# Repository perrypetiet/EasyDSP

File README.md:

# EasyDSP prototype_dev v0.1 development branch.
This is the EasyDSP prototype development library. In this repository you will find the hardware of the EasyDSP as well as the corresponding firmware. In this readme you will find an explanation of how to firmware functions and how to control the EasyDSP using the corresponding communication protocol. Also, you will find the PCB schematics and PCB design without the need to have KiCad and all the corresponding components on hand.

This readme will be updated to display correct and relevant information depending on the branch.

## Table of contents:
- [EasyDSP prototype\_dev v0.1 development branch.](#easydsp-prototype_dev-v01-development-branch)
  - [Table of contents:](#table-of-contents)
  - [Introduction ](#introduction-)
  - [TODO list ](#todo-list-)
  - [Controlling via BLE. ](#controlling-via-ble-)
  - [Python. ](#python-)
  - [Hardware ](#hardware-)

## Introduction 
The goal of this project is to make a cheap and easy to control module in order to do all your audio digital signal processing needs. The EasyDSP could be used for audio crossover, room correction, subwoofer tuning, using [Bass Eq](https://www.avsforum.com/threads/bass-eq-for-filtered-movies.2995212/) and much more. The goal of the project is to be able to control the EasyDSP using a Bluetooth low energy connection. When connected BLE characteristics can be used to control the EasyDSP. The basic structure of the signal processor can be explained with the following image:
</br></br>
The EasyDSP has two inputs and four outputs. The mux makes it possible to connect any input with any output. Every in and output has an equalizer to which five filters can be applied.</br>
The goal of the protoype is to implement the basic functioning of this system while doing it reliably. When this is achieved, functionality can be upgraded.

## TODO list 

- Make the settings store on the EEPROM. ✅
- Implement more filters (Bessel?) for better low pass and high pass.
- Maybe improve Python module for this verstion.

Things to include in next version:
- Better PCB design to improve the noise in the audio signal coming from the Bluetooth antenna (External antenna?).
- RGB status indication LED.
- Case design. (3D printable).
- Start working on GUI app for desktop to control the device.
- More functionality in firmware, more filters and gain control. And overall cleanup. 
- Thinking about serial control via USB.

## Controlling via BLE. 
Easydsp can be controlled with a BLE connection. The BLE implements two different services. The first service is a "selection" service. With this service the channel and eq number that are desired to be changed can be selected. With the channel number characteriscic you can change the channel number. With the isOutput characteristic you can select if it is an input or output channel that is selected. With the eq characteristic you can selected one of the 5 eq's per channel that you wish to change te settings of.

The EQ service implements the EQ data of the selected EQ on the selected channel. This service has characteristics to change the behaviour of the selected EQ. 

## Python. 
Included is a simple python module, easydsp.py, that can be used to control the easydsp over a BLE connection. I have also included a simple Python command line program that uses this module to control the EasyDSP.

## Hardware 
The EasyDSP is based on the ADAU1701 digital signal processor from Analog Devices. The chip is used in I2C control mode. This way, we can control the the signal processor from an external microcontroller during operation. The microcontroller used is an ESP32-S3 in the form a WROOM module to make development of the prototype hardware easier. The board and firmware have the ability to store the EQ, MUX and gain settings on an EEPROM. The EEPROM used is a 24LC128 in an MSOP package. Technically lower storage 24LC EEPROM's can also be used. In order to upload the firmware to the board, the USB connector on the PCB can be used. Firmware can also be uploaded and monitored using an external USB to UART PCB connected to the connector on the main PCB. There is an example board in the hardware folder. Following is the hardware schematic. The schematic can also be opened using KiCad.
</br></br>
The PCB fabrication files can be found in the hardware_design folder. Using these gerber and drill files you can order a PCB from a manufactorer.
</br></br>
</br></br>

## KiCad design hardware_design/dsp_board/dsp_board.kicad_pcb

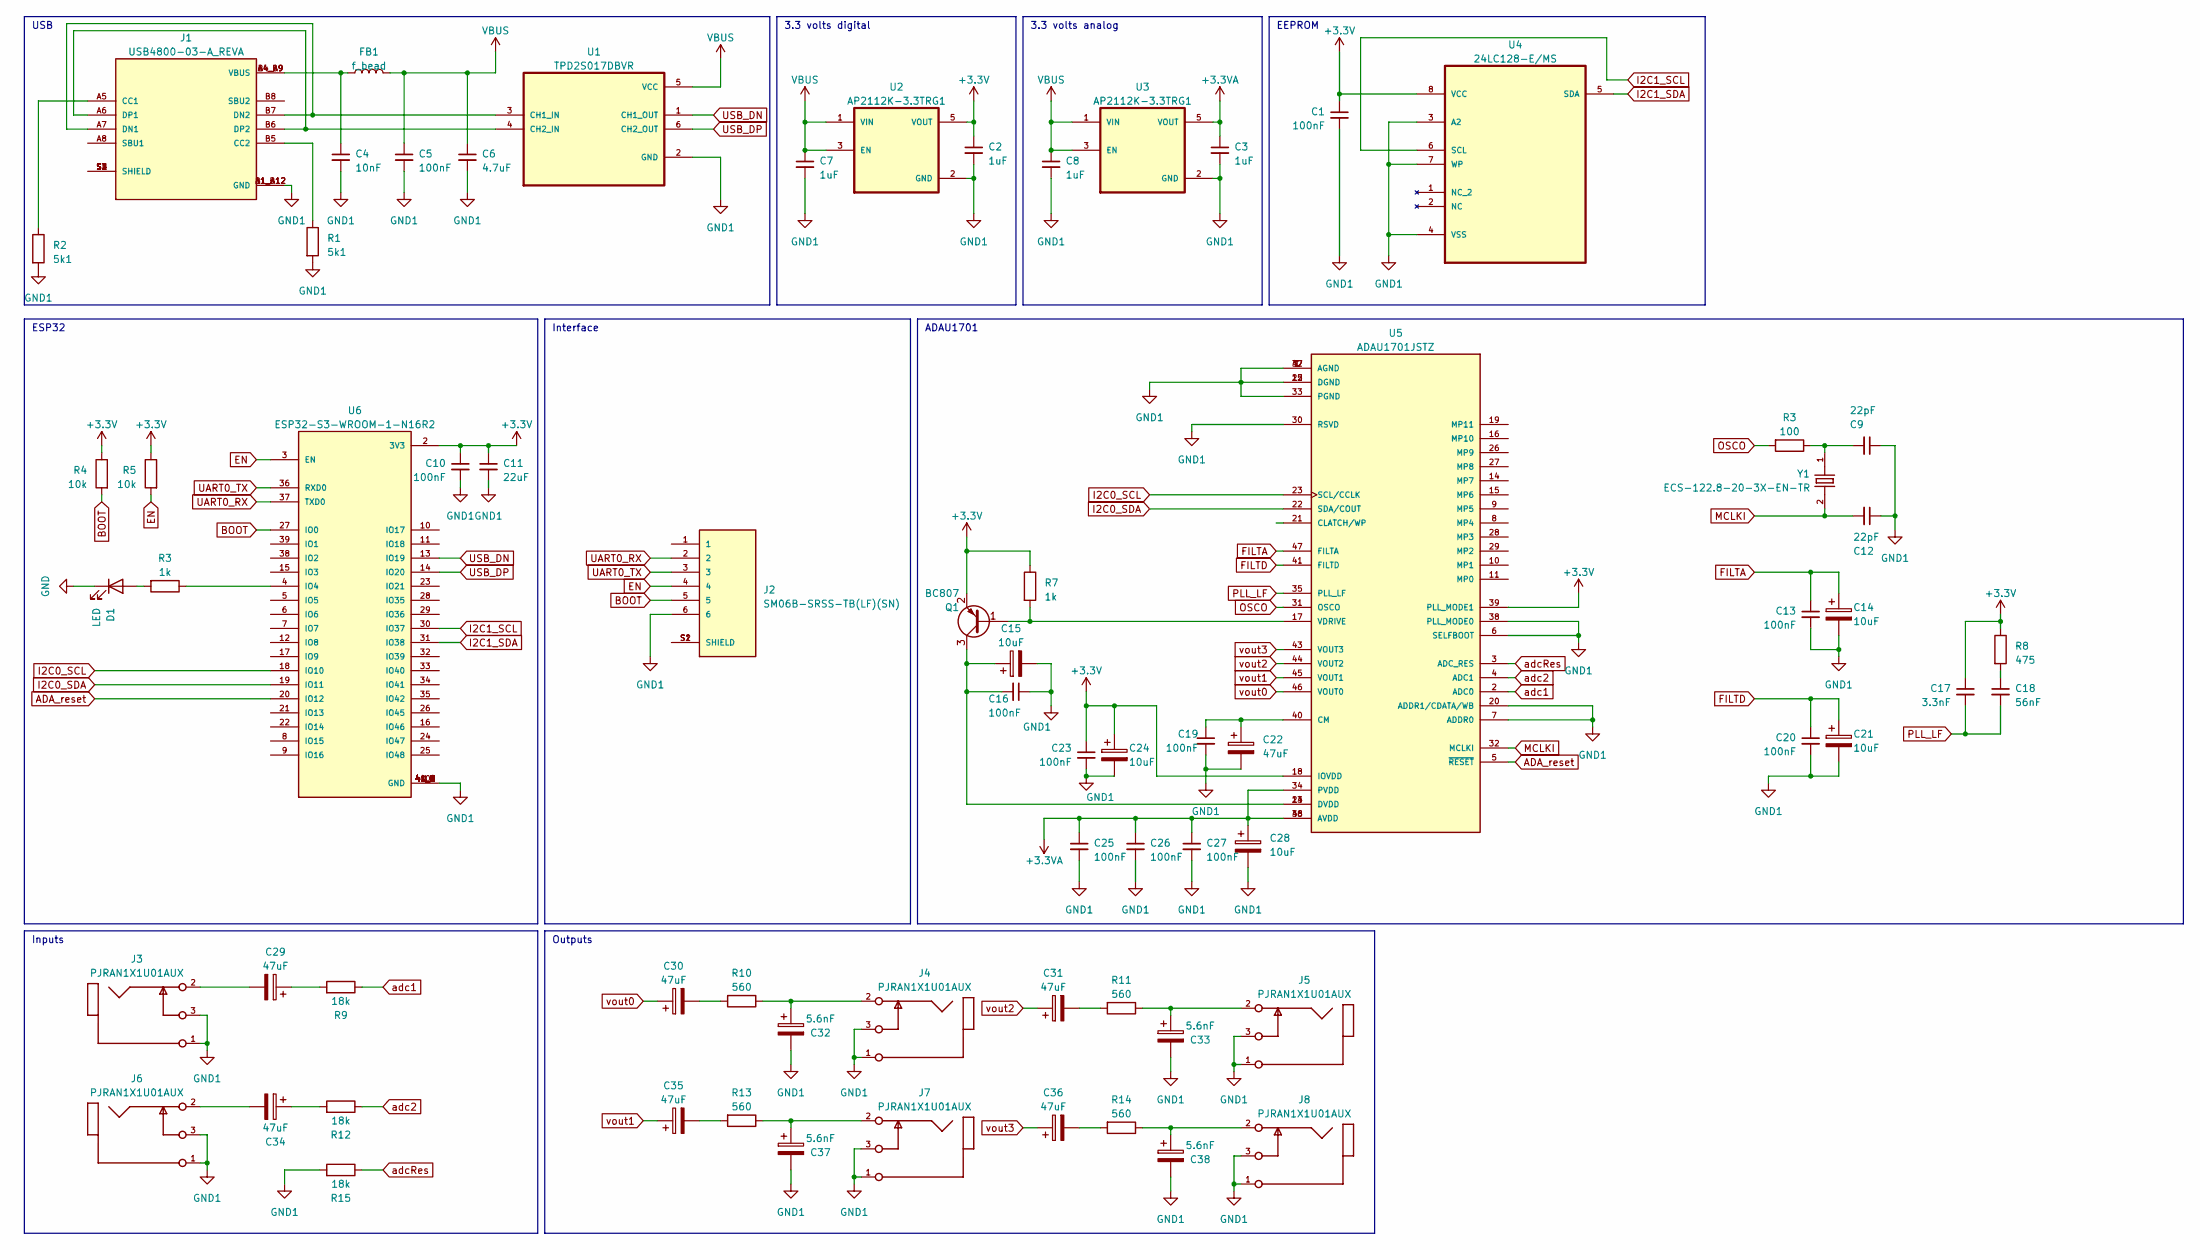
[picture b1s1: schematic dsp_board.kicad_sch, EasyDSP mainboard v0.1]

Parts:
C1, C5, C10, C13, C16, C19, C20, C23, C25, C26, C27: 100nF; C_0603_1608Metric
C2, C3, C7, C8: 1uF; C_0603_1608Metric
C4: 10nF; C_0603_1608Metric
C6: 4.7uF; C_0603_1608Metric
C9, C12: 22pF; C_0603_1608Metric
C11: 22uF; C_0603_1608Metric
C14, C15, C21, C24, C28: 10uF; CP_EIA-1608-08_AVX-J
C17: 3.3nF; C_0603_1608Metric
C18: 56nF; C_0603_1608Metric
C22, C29, C34: 47uF; CP_EIA-1608-08_AVX-J
C30, C31, C35, C36: 47uF; CP_Elec_5x4.5
C32, C33, C37, C38: 5.6nF; CP_EIA-1608-08_AVX-J
D1: LED; D_0603_1608Metric
FB1: f_bead; L_0805_2012Metric
J1: USB4800-03-A_REVA; GCT_USB4800-03-A_REVA; PARTREV A
J2: SM06B-SRSS-TB(LF)(SN); JST_SM06B-SRSS-TB(LF)(SN)
J3, J4, J5, J6, J7, J8: PJRAN1X1U01AUX; PJRAN1X1U01X
Q1: BC807; SOT-23
R1, R2: 5k1; R_0603_1608Metric
R3: 100; R_0603_1608Metric
R4, R5: 10k; R_0603_1608Metric
R7: 1k; R_0603_1608Metric
R8: 475; R_0603_1608Metric
R9, R12, R15: 18k; R_0603_1608Metric
R10, R11, R13, R14: 560; R_0603_1608Metric
U1: TPD2S017DBVR; SOT95P280X145-6N
U2, U3: AP2112K-3.3TRG1; SOT95P285X140-5N; PARTREV 2-2
U4: 24LC128-E/MS; SOP65P490X110-8N; MPN 24LC128-E/MS
U5: ADAU1701JSTZ; QFP50P900X900X160-48N; PARTREV C
U6: ESP32-S3-WROOM-1-N16R2; XCVR_ESP32-S3-WROOM-1-N16R2; PARTREV v1.0
Y1: ECS-122.8-20-3X-EN-TR; XTAL_ECS-122.8-20-3X-EN-TR; PARTREV 2017

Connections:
+3.3V: C1.1, C2.1, C10.1, C11.1, C17.1, C23.1, C24.1, Q1.2 (E), R4.1, R5.1, R7.1, R8.1, U2.5 (VOUT), U4.8 (VCC), U5.18 (IOVDD), U5.39 (PLL_MODE1), U6.2 (3V3)
+3.3VA: C3.1, C25.1, C26.1, C27.1, C28.1, U3.5 (VOUT), U5.34 (PVDD), U5.36 (AVDD), U5.48 (AVDD)
ADA_reset: U5.5 (~RESET), U6.20 (IO12)
BOOT: J2.5, R4.2, U6.27 (IO0)
EN: J2.4, R5.2, U6.3 (EN)
FILTA: C13.1, C14.1, U5.47 (FILTA)
FILTD: C20.1, C21.1, U5.41 (FILTD)
GND: D1.1 (K)
GND1: C1.2, C2.2, C3.2, C4.2, C5.2, C6.2, C7.2, C8.2, C9.1, C10.2, C11.2, C12.1, C13.2, C14.2, C15.2, C16.1, C19.2, C20.2, C21.2, C22.2, C23.2, C24.2, C25.2, C26.2, C27.2, C28.2, C32.2, C33.2, C37.2, C38.2, J1.A1_B12 (GND), J1.B1_A12 (GND), J2.6, J3.1, J3.3, J4.1, J4.3, J5.1, J5.3, J6.1, J6.3, J7.1, J7.3, J8.1, J8.3, R1.2, R2.2, R15.2, U1.2 (GND), U2.2 (GND), U3.2 (GND), U4.3 (A2), U4.4 (VSS), U4.7 (WP), U5.1 (AGND), U5.6 (SELFBOOT), U5.7 (ADDR0), U5.12 (DGND), U5.20 (ADDR1/CDATA/WB), U5.25 (DGND), U5.30 (RSVD), U5.33 (PGND), U5.37 (AGND), U5.38 (PLL_MODE0), U5.42 (AGND), U6.1 (GND), U6.40 (GND), U6.41_1 (GND), U6.41_2 (GND), U6.41_3 (GND), U6.41_4 (GND), U6.41_5 (GND), U6.41_6 (GND), U6.41_7 (GND), U6.41_8 (GND), U6.41_9 (GND)
I2C0_SCL: U5.23 (SCL/CCLK), U6.18 (IO10)
I2C0_SDA: U5.22 (SDA/COUT), U6.19 (IO11)
I2C1_SCL: U4.6 (SCL), U6.30 (IO37)
I2C1_SDA: U4.5 (SDA), U6.31 (IO38)
MCLKI: C12.2, U5.32 (MCLKI), Y1.2
unnamed: C4.1, FB1.1, J1.A4_B9 (VBUS), J1.B4_A9 (VBUS)
unnamed: C18.1, R8.2
unnamed: C29.1, R9.2
unnamed: C29.2, J3.2
unnamed: C30.2, R10.2
unnamed: C31.2, R11.2
unnamed: C32.1, J4.2, R10.1
unnamed: C33.1, J5.2, R11.1
unnamed: C34.1, R12.2
unnamed: C34.2, J6.2
unnamed: C35.2, R13.2
unnamed: C36.2, R14.2
unnamed: C37.1, J7.2, R13.1
unnamed: C38.1, J8.2, R14.1
unnamed: J1.A5 (CC1), R2.1
unnamed: J1.B5 (CC2), R1.1
unnamed: J1.A7 (DN1), J1.B7 (DN2), U1.3 (CH1_IN)
unnamed: J1.A6 (DP1), J1.B6 (DP2), U1.4 (CH2_IN)
unnamed: J1.S1 (SHIELD), J1.S2 (SHIELD), J1.S3 (SHIELD), J1.S4 (SHIELD)
unnamed: J2.S1 (SHIELD), J2.S2 (SHIELD)
unnamed: Q1.1 (B), R7.2, U5.17 (VDRIVE)
unnamed: C15.1, C16.2, Q1.3 (C), U5.13 (DVDD), U5.24 (DVDD)
unnamed: C19.1, C22.1, U5.40 (CM)
PLL_LF: C17.2, C18.2, U5.35 (PLL_LF)
UART0_RX: J2.2, U6.37 (TXD0)
UART0_TX: J2.3, U6.36 (RXD0)
USB_DN: U1.1 (CH1_OUT), U6.13 (IO19)
USB_DP: U1.6 (CH2_OUT), U6.14 (IO20)
VBUS: C5.1, C6.1, C7.1, C8.1, FB1.2, U1.5 (VCC), U2.1 (VIN), U2.3 (EN), U3.1 (VIN), U3.3 (EN)
adc1: R9.1, U5.2 (ADC0)
adc2: R12.1, U5.4 (ADC1)
adcRes: R15.1, U5.3 (ADC_RES)
vout0: C30.1, U5.46 (VOUT0)
vout1: C35.1, U5.45 (VOUT1)
vout2: C31.1, U5.44 (VOUT2)
vout3: C36.1, U5.43 (VOUT3)

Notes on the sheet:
Interface
Inputs
Outputs
ADAU1701
3.3 volts analog
3.3 volts digital
EEPROM
ESP32
USB

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
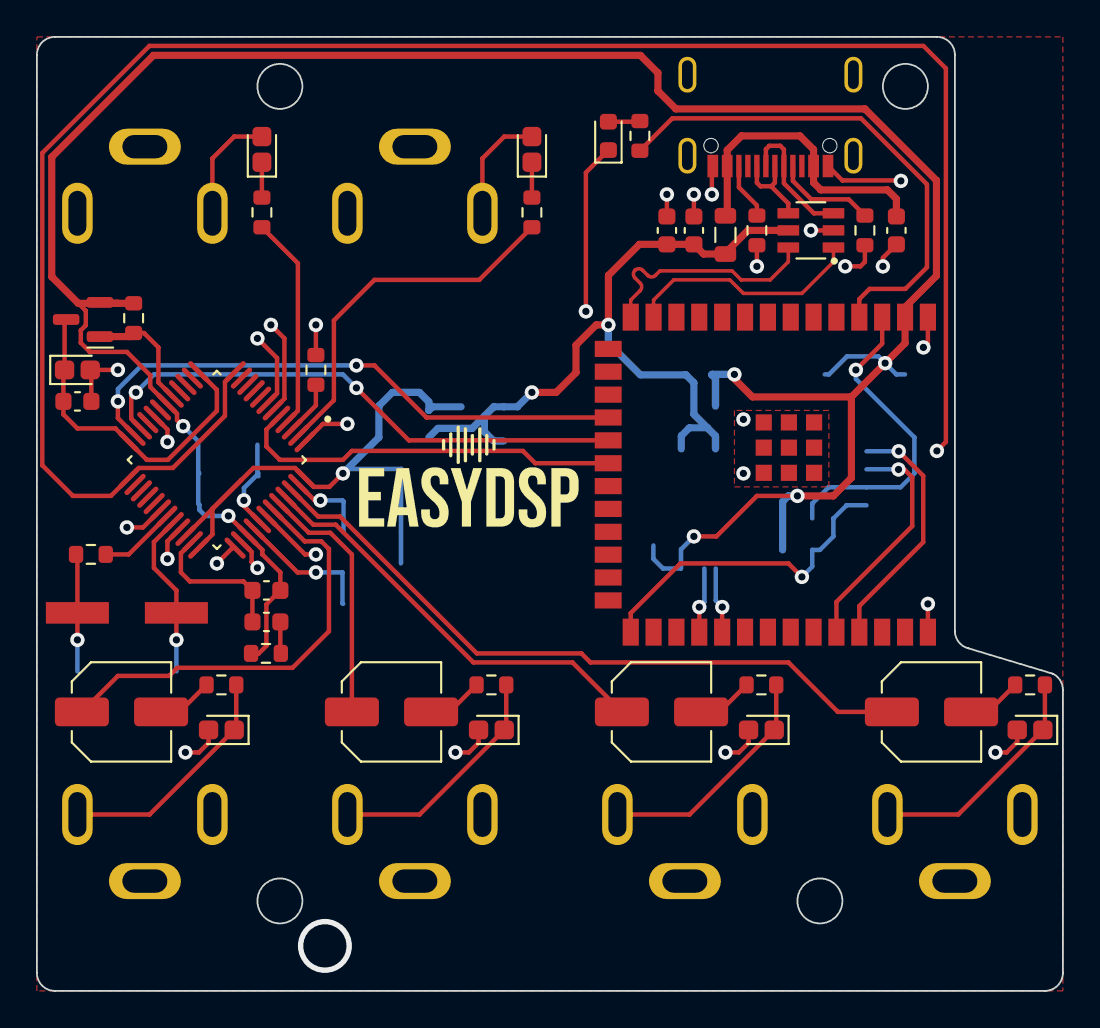
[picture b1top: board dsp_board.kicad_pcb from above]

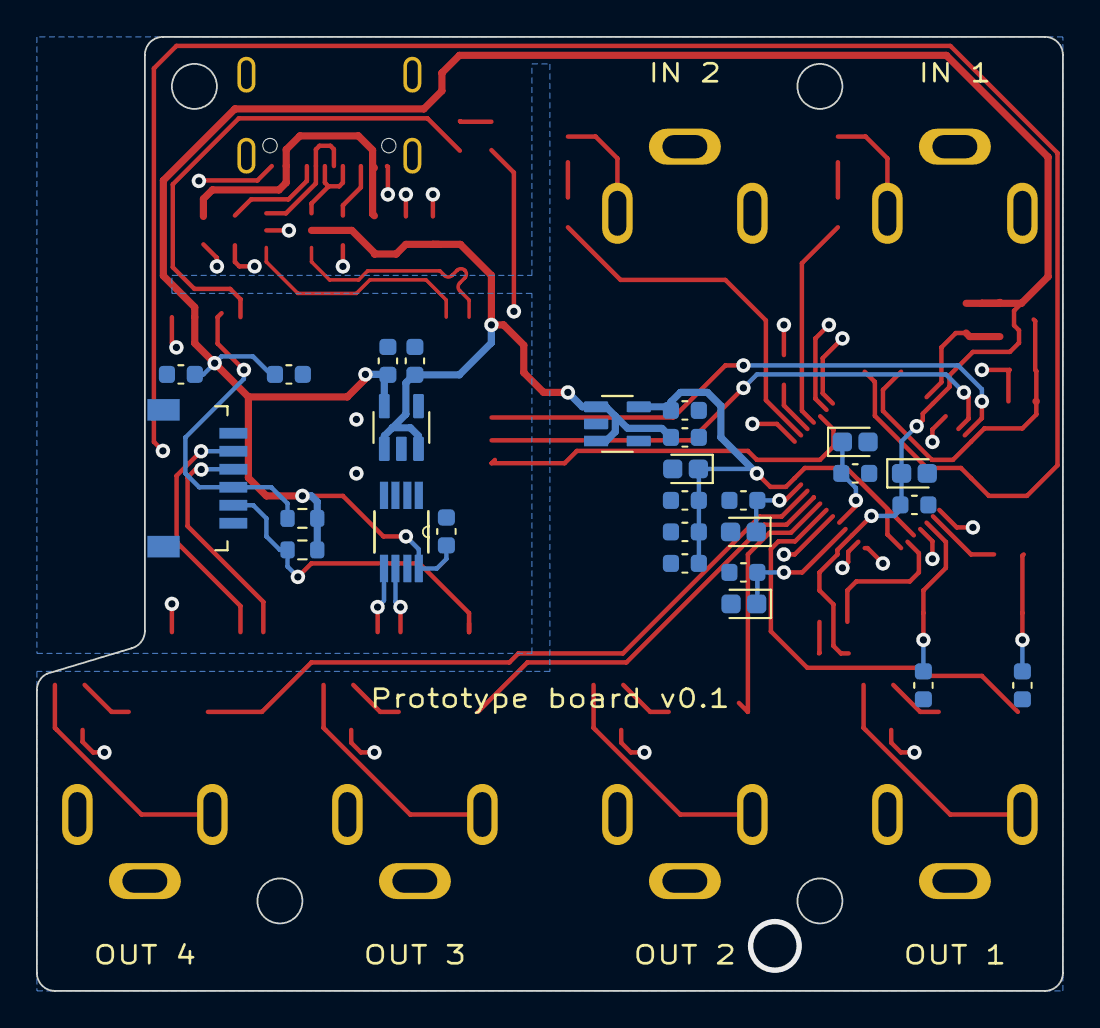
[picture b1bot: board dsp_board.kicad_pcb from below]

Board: 2 copper layers, 57.0 x 53.0 mm, 71 parts (27 on the bottom side), 53 nets.

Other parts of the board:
R6: 1k; R_0603_1608Metric

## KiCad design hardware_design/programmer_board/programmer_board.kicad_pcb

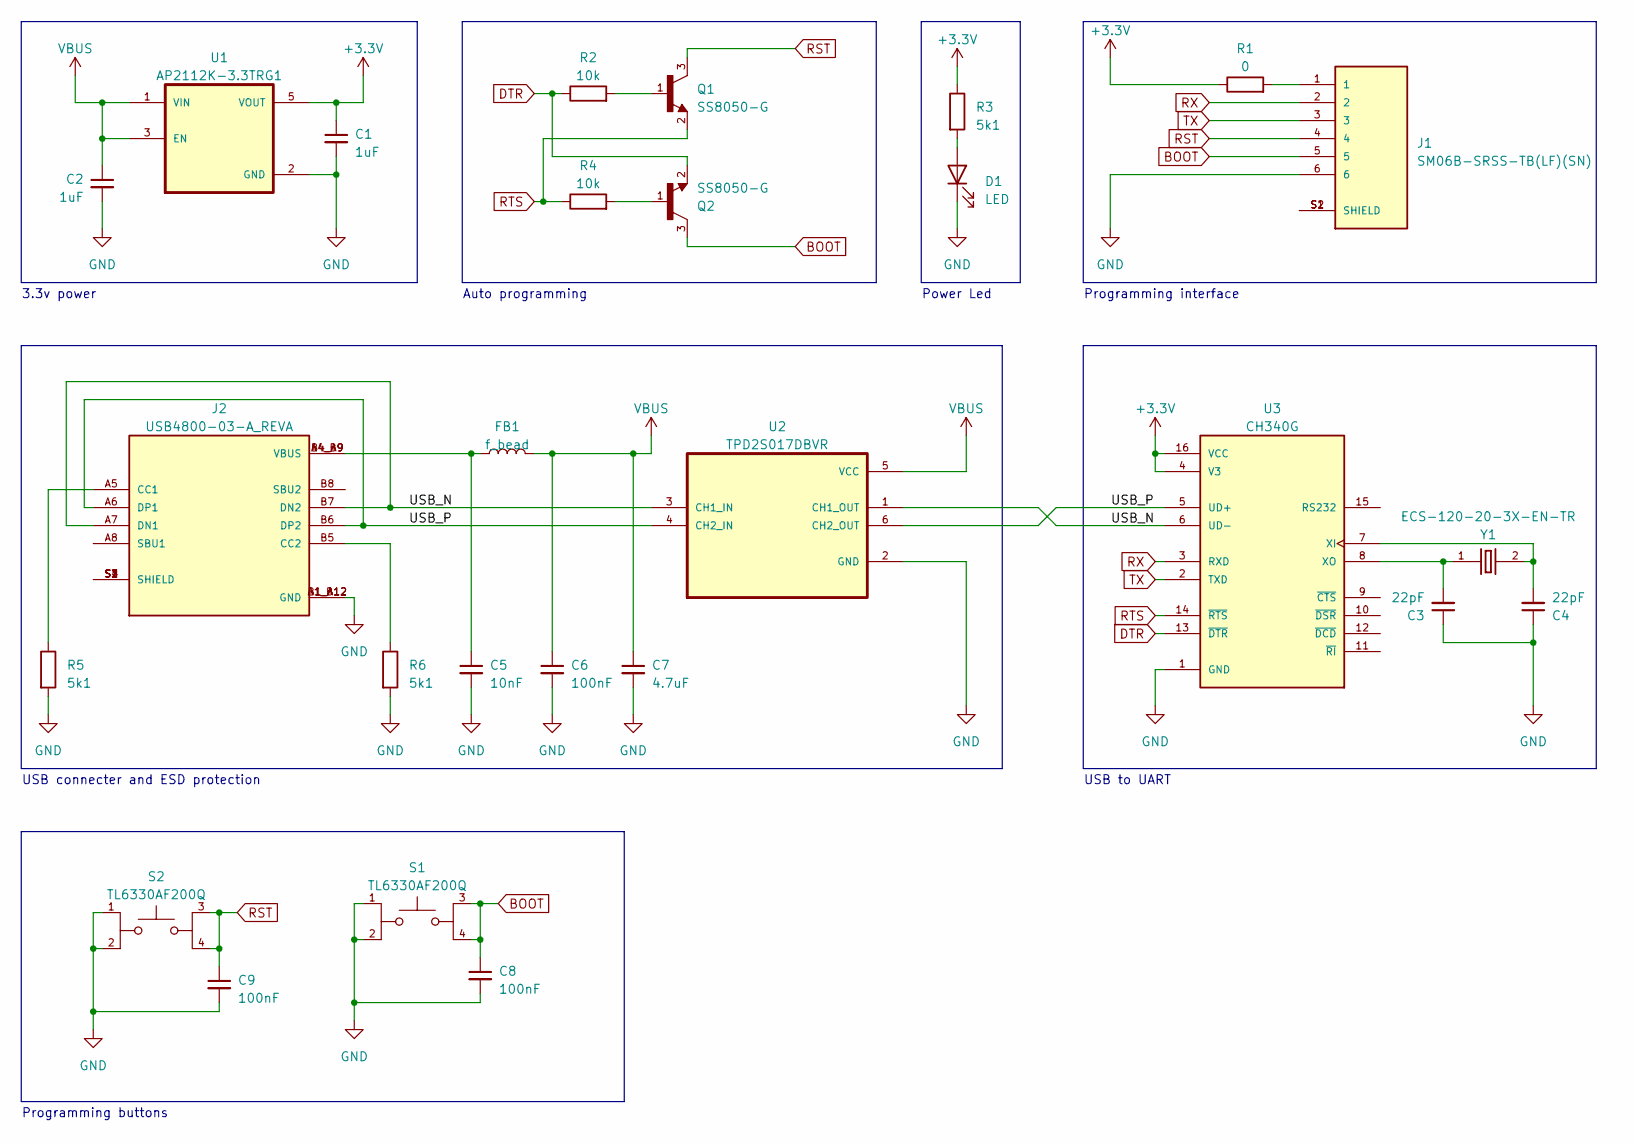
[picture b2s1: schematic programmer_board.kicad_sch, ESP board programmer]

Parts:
C1, C2: 1uF; C_0603_1608Metric
C3, C4: 22pF; C_0603_1608Metric
C5: 10nF; C_0603_1608Metric
C6, C8, C9: 100nF; C_0603_1608Metric
C7: 4.7uF; C_0603_1608Metric
D1: LED; D_0603_1608Metric
FB1: f_bead; L_0805_2012Metric
J1: SM06B-SRSS-TB(LF)(SN); JST_SM06B-SRSS-TB(LF)(SN)
J2: USB4800-03-A_REVA; GCT_USB4800-03-A_REVA; PARTREV A
Q1, Q2: SS8050-G; TRANS_SS8050-G; PARTREV A
R1: 0; R_0603_1608Metric
R2, R4: 10k; R_0603_1608Metric
R3, R5, R6: 5k1; R_0603_1608Metric
S1, S2: TL6330AF200Q; SW_TL6330AF200Q; PARTREV D
U1: AP2112K-3.3TRG1; SOT95P285X140-5N; PARTREV 2-2
U2: TPD2S017DBVR; SOT95P280X145-6N
U3: CH340G; SOIC127P600X180-16N; PARTREV 2G
Y1: ECS-120-20-3X-EN-TR; XTAL_ECS-120-20-3X-EN-TR; PARTREV 2017

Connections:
+3.3V: C1.1, R1.1, R3.1, U1.5 (VOUT), U3.4 (V3), U3.16 (VCC)
/USB_N: J2.A7 (DN1), J2.B7 (DN2), U2.1 (CH1_OUT), U2.3 (CH1_IN), U3.6 (UD-)
/USB_P: J2.A6 (DP1), J2.B6 (DP2), U2.4 (CH2_IN), U2.6 (CH2_OUT), U3.5 (UD+)
BOOT: C8.1, J1.5, Q2.3, S1.3, S1.4
DTR: Q2.2, R2.1, U3.13 (~DTR)
GND: C1.2, C2.2, C3.1, C4.1, C5.2, C6.2, C7.2, C8.2, C9.2, D1.1 (K), J1.6, J2.A1_B12 (GND), J2.B1_A12 (GND), R5.2, R6.2, S1.1, S1.2, S2.1, S2.2, U1.2 (GND), U2.2 (GND), U3.1 (GND)
unnamed: C5.1, FB1.1, J2.A4_B9 (VBUS), J2.B4_A9 (VBUS)
unnamed: D1.2 (A), R3.2
unnamed: J1.1, R1.2
unnamed: J1.S1 (SHIELD), J1.S2 (SHIELD)
unnamed: J2.A5 (CC1), R5.1
unnamed: J2.B5 (CC2), R6.1
unnamed: J2.S1 (SHIELD), J2.S2 (SHIELD), J2.S3 (SHIELD), J2.S4 (SHIELD)
unnamed: Q1.1, R2.2
unnamed: Q2.1, R4.2
unnamed: C4.2, U3.7 (XI), Y1.2
unnamed: C3.2, U3.8 (XO), Y1.1
RST: C9.1, J1.4, Q1.3, S2.3, S2.4
RTS: Q1.2, R4.1, U3.14 (~RTS)
RX: J1.2, U3.3 (RXD)
TX: J1.3, U3.2 (TXD)
VBUS: C2.1, C6.1, C7.1, FB1.2, U1.1 (VIN), U1.3 (EN), U2.5 (VCC)

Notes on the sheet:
3.3v power
Programming interface
Auto programming
USB to UART
USB connecter and ESD protection
Programming buttons
Power Led

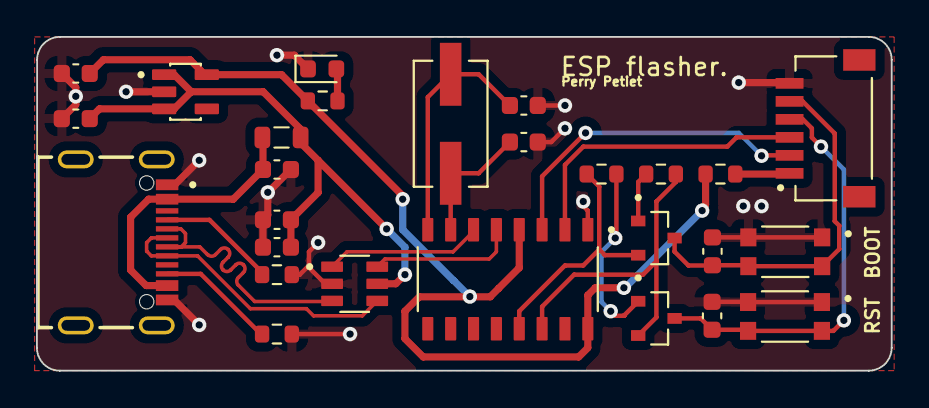
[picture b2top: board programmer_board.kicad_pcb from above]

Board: 2 copper layers, 47.5 x 18.5 mm, 27 parts (0 on the bottom side), 22 nets.

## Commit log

2023-07-21 Created hardware project files
    Created hardware project files
2023-07-21 Added footprints
    Added some footprints for development of hardware
2023-07-21 Started design programmer board
2023-07-21 Updated programmer schematic
    Started development on programmer schematic
2023-07-21 Finished programmer schematic
    Programmer schematic drawn. Review.
2023-07-21 Started programmer pcb design
    Started programmer PCB design
2023-07-21 Almost routed programmer board
2023-07-21 Create test
2023-07-21 Made esp-idf project
2023-07-21 Created project for firmware
2023-07-21 Setting up workspace
2023-07-24 Programmer board progress
2023-07-24 Sigmastudio test project
    Created sigmastudio project for the DSP
2023-07-24 Tested parameter header file generation
    Tested the generation of the header file from a sigmastudio project using an existing script. Working! can upload a sigmastudio project using MCUdudes library.
2023-08-07 Programmer board PCB
    Programmer board PCB finished.
2023-08-31 fed around with FreeRTOS tasks
2023-10-20 backup
    backup
2023-10-27 EEPROM module development
2023-10-30 device settings storage
    Implemented basic library to store device settings on eeprom
2023-10-30 added gitignore
2023-10-30 test
2023-10-30 Gitignore working
2023-10-31 Started devlopment sigma dsp module
    Started the development on the sigma dsp module and fixed some issues with the eeprom module.
2023-10-31 started main board design
2023-11-06 Task testing
    Played around with FreeRTOS tasks and looked over device settings code to gain ideas for improvement.
2023-11-07 Program loading implemented
    Implemented the loading of the DSP program to the ADAU1701 using i2c and the exported files from sigma studio. Also fixed memory issue with i2c. The making om i2c commands should be improved. (No for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
2023-11-07 Changed settings storage
2023-11-08 Second order eq implemented
2023-11-09 Implemented MUX control
2023-11-09 Mux functionality added, added dsp addresses to device settings.
2023-11-10 Started PCB design
2023-11-13 Queues
2023-11-13 Loading settings
    Settings task now sends all settings to dsp task after initialisation.
2023-11-15 Functional design
    Changed functional design drawing of firmware
2023-11-16 Improved PCB
    Improved main PCB design
2023-11-17 Mainboard progress
    Layout progress on prototype mainboard
2023-11-19 PCB layout complete
    PCB layout and routing complete.
2023-11-19 Create README.md
    Created a readme file for documentation
2023-11-19 Deleted some files
2023-11-19 Documentation start
2023-11-20 Silkscreen improvements
2023-11-20 Updated font
2023-11-20 Disabled references
2023-11-20 Fixed logo
2023-11-20 Changed RCA connectors
2023-11-20 PCB concept finished
2023-11-20 documentation update
2023-11-20 Documentation fix
2023-11-21 Events
    Implemented basic events between tasks. The settings task can now send events to the DSP task and wait for a response from the DSP task. using easy function calls and datatypes.
2023-11-22 Started protocol documentation.
2023-11-23 Start protocol documentation
2023-11-24 Enabled BLE
    Enabled BLE in config. Can now use BLE includes from ESP-IDF
2023-12-07 Started BLE work
    Started work on the BLE interface. Initialisation working.
2024-01-17 fixed typo
2024-01-20 naming
2024-01-29 Implemented BLE advertising
2024-02-10 Started BLE buffering
2024-02-18 started buffering task
2024-02-24 New export
    New gerber export for production. Different via's.
2024-03-16 Buffering BLE
    Implemented the buffers for the BLE interface
2024-03-26 started buffering
2024-08-17 LED driver
    Created LED driver for indicating the ble connection state.
2024-08-27 Ble scanner
    Simple ble scanner for debugging purposes
2024-10-03 Started BLE interface working
    Setup the basic structure for the BLE interface working. Settings task now accepts events from the BLE task.
2024-10-15 Worked on BLE interfacing.
    Setting the channel index characteristic now updates the active mux and eq data in ble interface based on teh channel index and eq index.
2024-10-19 BLE interfacing complete.
    BLE interfacing complete. Needs final testing.
2024-10-21 Ble terminal development
    Can now connect to BLE device from python easydsp_cmd.py
    For this prototype this will be the main control software
2024-11-04 Python command interface
    Command interface almost finished. todo: convert everything to floats only.
2024-11-19 Python module improvement
    Python BLE module improvement. Data now gets always send as uint32
2024-11-23 ident change to 2 spaces
    Ident changed to 2 spaces for better readability.
2024-11-23 Doc and cleanup.
2024-11-25 NV storage
    Settings now get stored in NV ram.
2024-12-22 dsp addressing easier + error led
2024-12-29 Improved dsp addressing
